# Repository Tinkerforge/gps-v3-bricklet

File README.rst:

GPS Bricklet 3.0
================

**This Bricklet is currently in development.**

This repository contains the firmware source code and the hardware design
files. The documentation generator configs can be found at
https://github.com/Tinkerforge/generators

Repository Content
------------------

software/:
 * examples/: Examples for all supported languages
 * build/: Compiled files
 * src/: Source code of firmware
 * Makefile: Makefile to build project

hardware/:
 * Contains KiCad project files and additionally schematics as PDF

datasheets/:
 * Contains datasheets for sensors and complex ICs that are used

Hardware
--------

The hardware is designed with the open source EDA Suite KiCad
(http://www.kicad.org). Before you are able to open the files,
you have to install the Tinkerforge kicad-libraries
(https://github.com/Tinkerforge/kicad-libraries). You can either clone
them directly in hardware/ or clone them in a separate folder and
symlink them into hardware/
(ln -s kicad_path/kicad-libraries project_path/hardware). After that you
can open the .pro file in hardware/ with KiCad and from there view and
modify the schematics and the PCB layout.

Software
--------

If you want to do your own Brick/Bricklet firmware development we highly
recommend that you use our build environment setup script and read the
tutorial (https://www.tinkerforge.com/en/doc/Tutorials/Tutorial_Build_Environment/Tutorial.html).

To compile the C code we recommend you to install the newest GNU Arm Embedded
Toolchain (https://launchpad.net/gcc-arm-embedded/+download).
You also need to install bricklib2 (https://github.com/Tinkerforge/bricklib2).

You can either clone it directly in software/src/ or clone it in a
separate folder and symlink it into software/src/
(ln -s bricklib_path/bricklib2 project_path/software/src/). Finally make sure to
have CMake installed (http://www.cmake.org/cmake/resources/software.html).

After that you can build the firmware by invoking make in software/.
The firmware (.zbin) can then be found in software/build/ and uploaded
with brickv (click button "Flashing" on start screen).

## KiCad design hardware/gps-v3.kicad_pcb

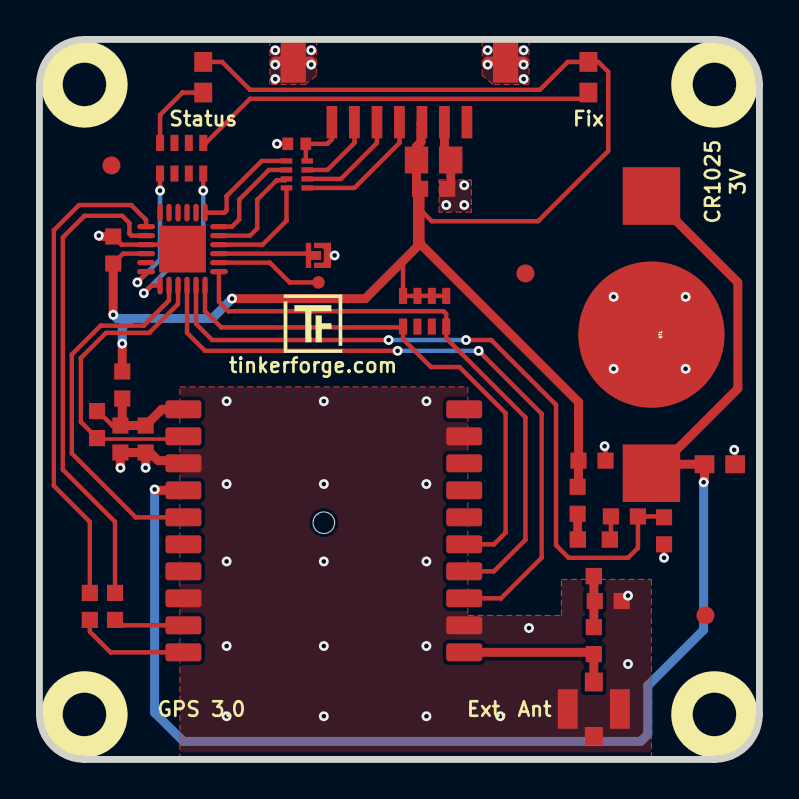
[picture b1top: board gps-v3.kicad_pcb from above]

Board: 2 copper layers, 40.0 x 40.0 mm, 39 parts (2 on the bottom side), 32 nets.

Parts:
BT1: CR1025 3V; BATTERY_HOLDER_BK870
C1: 220pF; C0402F
C2: 1uF; C0603E
C3, C101: 1uF; C0603F
C4, C103: 100nF; C0603F
C5, C6: DNP; C0603F
C102: 10uF; C0805E
D1: LED green; D0603E
D101: LED blue; D0603E
Fiducial_Mark: VAL**; Fiducial_Mark
Fiducial_Mark#2, Fiducial_Mark#3: VAL**; Fiducial_Mark
L1: FB; R0603F
L2: DNP; 0603F
L3: DNP; R0603F
P1: Debug; DEBUG_PAD
P101: CON-SENSOR; CON-SENSOR2
P103: Boot; SolderJumper
P104: U.FL; U.FL-CON
Q1: DNP; SOT23GDS
R1: 10k; R0603F
R2, R3: 470; R0603F
R4, R5: DNP; R0603F
RP1: 82; 4X0402
RP2: 1k; 4X0603
RP3: 4,7k; 4X0603
U1: PA1616D
U101: XMC1302-32; QFN24-4x4mm-0.5mm
U103, U104, U105, U106: DRILL; DRILL_NP
VAL: WEEE_7mm
VAL#2: CE_5mm

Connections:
1PPS: U1.13, U101.16
3D_FIX: U1.5, U101.14
ANT_SWITCH: R4.1, R5.1, U101.17
GND: BT1.2, C1.2, C2.1, C3.1, C4.1, C5.1, C6.1, C101.1, C102.1, C103.1, P101.2, P101.EP, P103.1, P104.2, R5.2, U1.3, U1.8, U1.12, U1.19, U101.9, U101.EXP
unnamed: BT1.1, C2.2, U1.4
unnamed: C1.1, P101.7, RP1.4
unnamed: C3.2, C4.2, L1.1, R1.2, U1.1
unnamed: C5.2, L2.1, Q1.D
unnamed: D1.2, RP2.8
unnamed: D101.2, RP2.5
unnamed: L2.2, P104.1, U1.11
unnamed: L3.1, Q1.S
unnamed: P1.1, U101.20
unnamed: P101.4, RP1.1
unnamed: P101.5, RP1.2
unnamed: P101.6, RP1.3
unnamed: P103.2, U101.21
unnamed: Q1.G, R4.2
unnamed: R2.2, U1.9
unnamed: R3.2, U1.10
unnamed: RP2.1, U101.13
unnamed: RP2.4, U101.12
RESET: R1.1, U1.2, U101.15
RXD: R3.1, U101.7
S-CLK: RP1.7, U101.23
S-CS: RP1.8, U101.22
S-MISO: RP1.5, U101.1
S-MOSI: RP1.6, U101.24
SCL: RP3.5, U1.14, U101.19
SDA: RP3.8, U1.15, U101.18
TXD: R2.1, U101.8
VCC: C6.2, C101.2, C102.2, C103.2, D1.1, D101.1, L1.2, L3.2, P101.3, RP3.1, RP3.2, RP3.3, RP3.4, U101.10

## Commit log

2020-10-14 first schematic
2020-10-15 ready for prototype
2020-10-15 changed resistor value
2020-10-28 prototype
2022-01-13 Add GPS Bricklet 3.0 firmware implementation
2022-01-14 bugfix: change n ch mosfet with p ch mosfet
2022-01-14 Remove antenna config
2022-01-14 Remove debug
2022-01-14 make power boost circuitry as DNP
2022-05-10 Add examples
2022-05-10 go: Fix format string
2022-05-10 Make sure that baudrate change command was send
2022-06-24 Make sure uart send buffer is empty before we change the baudrate
2022-06-28 Wait 1s on boot before PA1616D initialization
2022-07-01 add 3d files and schematic
2022-07-04 fix name
2022-07-06 Add license files.
2023-03-16 Add LabVIEW examples
2023-12-18 Update changelog

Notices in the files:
hardware/gps-v3.kicad_pcb:
Licensed under CERN OHL v.1.1
Copyright (©) 2020, T.Schneidermann
Copyright Tinkerforge GmbH 2020.
This documentation describes Open Hardware and is licensed under the
CERN OHL v. 1.1.
